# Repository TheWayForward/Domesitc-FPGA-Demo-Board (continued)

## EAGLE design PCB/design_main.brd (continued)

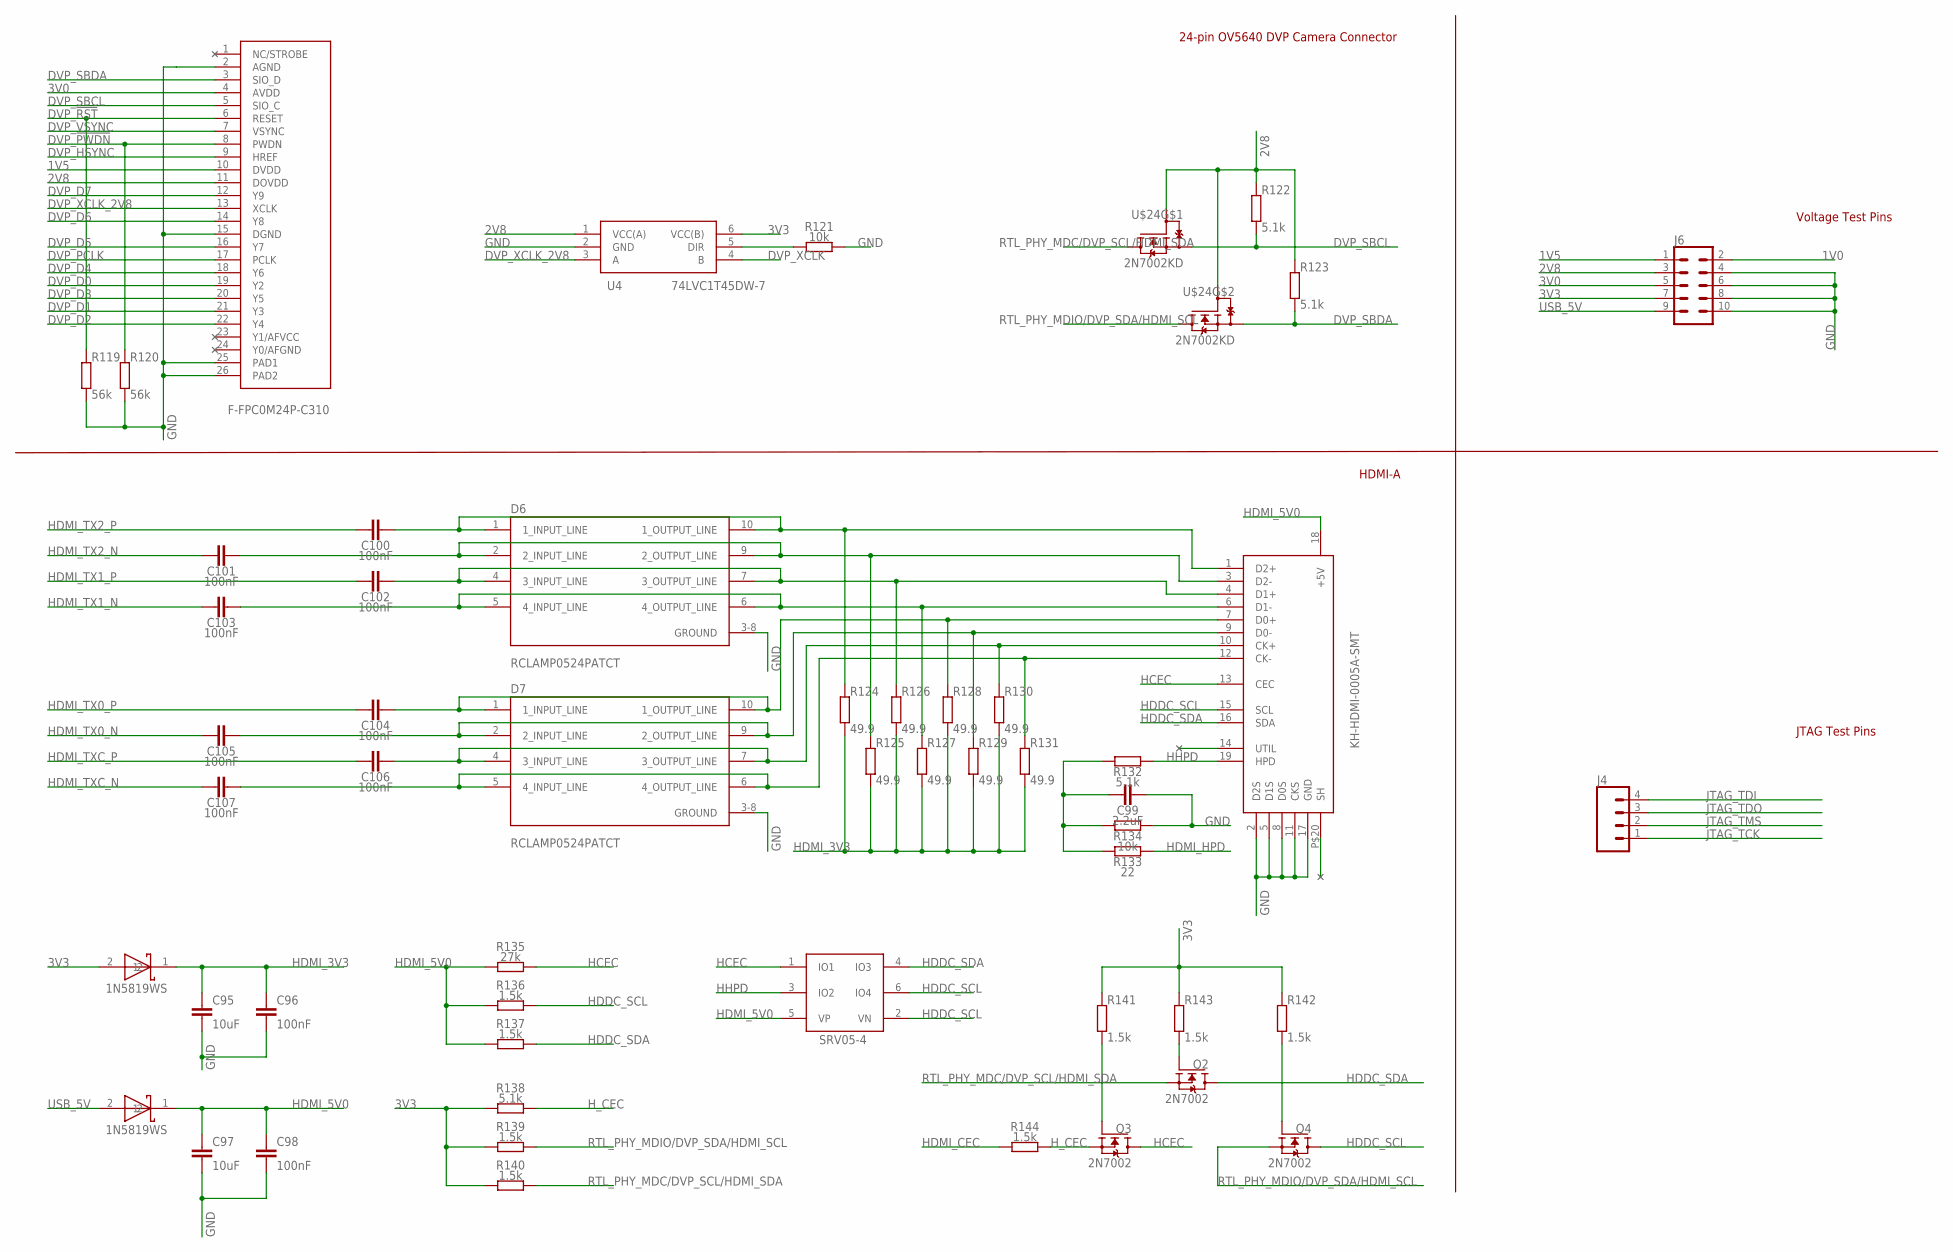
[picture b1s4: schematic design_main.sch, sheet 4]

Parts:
C95, C97: 10uF; C0805
C96, C98, C100, C101, C102, C103, C104, C105, C106, C107: 100nF; C0805
C99: 2.2uF; C0805
D6, D7: SEMTECH_RCLAMP0524PATCTSEMTECH_RCLAMP0524PATCT_0_0; SEMTECH_RCLAMP0524PATCT_0
J4: CONN_04PTH; 1X04
J6: CONN_05X2PTH; 2X5
Q2, Q3, Q4: 2N7002; SOT95P240X111-3N
R119, R120: 56k; R0805
R121, R134: 10k; R0805
R122, R123, R132, R138: 5.1k; R0805
R124, R125, R126, R127, R128, R129, R130, R131: 49.9; R0805
R133: 22; R0805
R135: 27k; R0805
R136, R137, R139, R140, R141, R142, R143, R144: 1.5k; R0805
U4: 74LVC1T45DW-7; SOT65P210X110-6N
U$23: F-FPC0M24P-C310
U$24: 2N7002KD
U$25, U$26: 1N5819WS
U$27: KH-HDMI-0005A-SMT
U$28: SRV05-4

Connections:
1V0: J6.2; also elsewhere on the board
1V5: J6.1, U$23.10 (DVDD); also elsewhere on the board
2V8: J6.3, R122.2, R123.2, U4.1 (VCC(A)), U$23.11 (DOVDD), U$24.P$2 (G1), U$24.P$5 (G2); also elsewhere on the board
3V0: J6.5, U$23.4 (AVDD); also elsewhere on the board
3V3: J6.7, R138.1, R139.1, R140.1, R141.1, R142.1, R143.1, U4.6 (VCC(B)), U$25.2; also elsewhere on the board
DVP_!PWDN!: R120.1, U$23.8 (PWDN); also elsewhere on the board
DVP_!RST!: R119.1, U$23.6 (RESET); also elsewhere on the board
DVP_D0: U$23.19 (Y2); also elsewhere on the board
DVP_D1: U$23.21 (Y3); also elsewhere on the board
DVP_D2: U$23.22 (Y4); also elsewhere on the board
DVP_D3: U$23.20 (Y5); also elsewhere on the board
DVP_D4: U$23.18 (Y6); also elsewhere on the board
DVP_D5: U$23.16 (Y7); also elsewhere on the board
DVP_D6: U$23.14 (Y8); also elsewhere on the board
DVP_D7: U$23.12 (Y9); also elsewhere on the board
DVP_HSYNC: U$23.9 (HREF); also elsewhere on the board
DVP_PCLK: U$23.17 (PCLK); also elsewhere on the board
DVP_SBCL: R122.1, U$23.5 (SIO_C), U$24.P$1 (S1)
DVP_SBDA: R123.1, U$23.3 (SIO_D), U$24.P$4 (S2)
DVP_VSYNC: U$23.7 (VSYNC); also elsewhere on the board
DVP_XCLK: U4.4 (B); also elsewhere on the board
DVP_XCLK_2V8: U4.3 (A), U$23.13 (XCLK)
GND: C95.1, C96.1, C97.1, C98.1, C99.1, D6.3-8 (GROUND), D7.3-8 (GROUND), J6.4, J6.6, J6.8, J6.10, R119.2, R120.2, R121.2, R134.2, U4.2 (GND), U$23.2 (AGND), U$23.15 (DGND), U$23.25 (PAD1), U$23.26 (PAD2), U$27.2 (D2S), U$27.5 (D1S), U$27.8 (D0S), U$27.11 (CKS), U$27.17 (GND); also elsewhere on the board
HCEC: Q3.3 (D), R135.2, U$27.13 (CEC), U$28.1 (IO1)
HDDC_SCL: Q4.3 (D), R136.2, U$27.15 (SCL), U$28.2 (VN), U$28.6 (IO4)
HDDC_SDA: Q2.3 (D), R137.2, U$27.16 (SDA), U$28.4 (IO3)
HDMI_3V3: C95.2, C96.2, R124.2, R125.2, R126.2, R127.2, R128.2, R129.2, R130.2, R131.2, U$25.1
HDMI_5V0: C97.2, C98.2, R135.1, R136.1, R137.1, U$26.1, U$27.18 (+5V), U$28.5 (VP)
HDMI_CEC: R144.1; also elsewhere on the board
HDMI_HPD: R133.2; also elsewhere on the board
HDMI_TX0_N: C105.2; also elsewhere on the board
HDMI_TX0_P: C104.2; also elsewhere on the board
HDMI_TX1_N: C103.2; also elsewhere on the board
HDMI_TX1_P: C102.2; also elsewhere on the board
HDMI_TX2_N: C101.2; also elsewhere on the board
HDMI_TX2_P: C100.2; also elsewhere on the board
HDMI_TXC_N: C107.2; also elsewhere on the board
HDMI_TXC_P: C106.2; also elsewhere on the board
HHPD: R132.2, U$27.19 (HPD), U$28.3 (IO2)
H_CEC: Q3.2 (S), R138.2, R144.2
JTAG_TCK: J4.1; also elsewhere on the board
JTAG_TDI: J4.4; also elsewhere on the board
JTAG_TDO: J4.3; also elsewhere on the board
JTAG_TMS: J4.2; also elsewhere on the board
unnamed: R121.1, U4.5 (DIR)
unnamed: C100.1, D6.1 (1_INPUT_LINE), D6.10 (1_OUTPUT_LINE), R124.1, U$27.1 (D2+)
unnamed: C101.1, D6.2 (2_INPUT_LINE), D6.9 (2_OUTPUT_LINE), R125.1, U$27.3 (D2-)
unnamed: C102.1, D6.4 (3_INPUT_LINE), D6.7 (3_OUTPUT_LINE), R126.1, U$27.4 (D1+)
unnamed: C103.1, D6.5 (4_INPUT_LINE), D6.6 (4_OUTPUT_LINE), R127.1, U$27.6 (D1-)
unnamed: C104.1, D7.1 (1_INPUT_LINE), D7.10 (1_OUTPUT_LINE), R128.1, U$27.7 (D0+)
unnamed: C105.1, D7.2 (2_INPUT_LINE), D7.9 (2_OUTPUT_LINE), R129.1, U$27.9 (D0-)
unnamed: C106.1, D7.4 (3_INPUT_LINE), D7.7 (3_OUTPUT_LINE), R130.1, U$27.10 (CK+)
unnamed: C107.1, D7.5 (4_INPUT_LINE), D7.6 (4_OUTPUT_LINE), R131.1, U$27.12 (CK-)
unnamed: C99.2, R132.1, R133.1, R134.1
unnamed: Q2.1 (G), R143.2
unnamed: Q3.1 (G), R141.2
unnamed: Q4.1 (G), R142.2
RTL_PHY_MDC/DVP_SCL/HDMI_SDA: Q2.2 (S), R140.2, U$24.P$6 (D1); also elsewhere on the board
RTL_PHY_MDIO/DVP_SDA/HDMI_SCL: Q4.2 (S), R139.2, U$24.P$3 (D2); also elsewhere on the board
USB_5V: J6.9, U$26.2; also elsewhere on the board

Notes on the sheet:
24-pin OV5640 DVP Camera Connector
HDMI-A
Voltage Test Pins
JTAG Test Pins

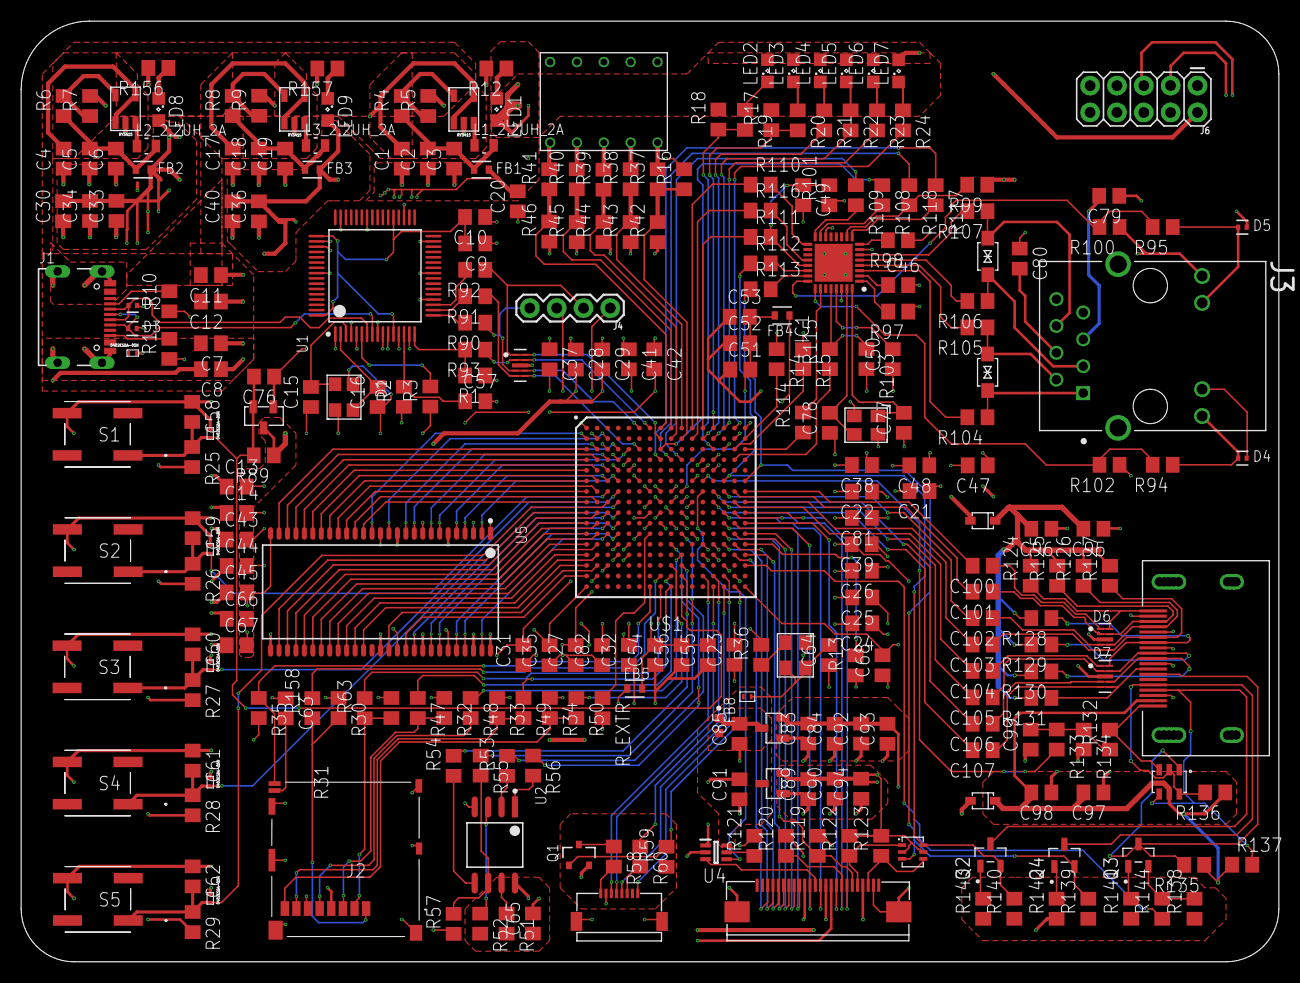
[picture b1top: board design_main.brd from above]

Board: 4 copper layers, 119.0 x 89.0 mm, 288 parts (0 on the bottom side), 235 nets.

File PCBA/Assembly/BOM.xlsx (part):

Description | Comment | Designator | Footprint | 编号
贴片电阻 | 1kΩ | R1 | R0805 | C17513
贴片电阻 | 10kΩ | R2 | R0805 | C844893
贴片电阻 | 12kΩ | R3 | R0805 | C706254
贴片电阻 | 680kΩ | R4 | R0805 | C445667
贴片电阻 | 150kΩ | R5 | R0805 | C17470
贴片电阻 | 150kΩ | R6 | R0805 | C17470
贴片电阻 | 100kΩ | R7 | R0805 | C161786
贴片电阻 | 100kΩ | R8 | R0805 | C161786
贴片电阻 | 150kΩ | R9 | R0805 | C17470
贴片电阻 | 5.1kΩ | R10 | R0805 | C2094165
贴片电阻 | 5.1kΩ | R11 | R0805 | C2094165
贴片电阻 | 220Ω | R12 | R0805 | C445664
贴片电阻 | 4.7kΩ | R13 | R0805 | C17673
贴片电阻 | 4.7kΩ | R14 | R0805 | C17673
贴片电阻 | 4.7kΩ | R15 | R0805 | C17673
贴片电阻 | 4.7kΩ | R16 | R0805 | C17673
贴片电阻 | 4.7kΩ | R17 | R0805 | C17673
贴片电阻 | 4.7kΩ | R18 | R0805 | C17673
贴片电阻 | 510Ω | R19 | R0805 | C17734
贴片电阻 | 510Ω | R20 | R0805 | C17734
贴片电阻 | 510Ω | R21 | R0805 | C17734
贴片电阻 | 510Ω | R22 | R0805 | C17734
贴片电阻 | 510Ω | R23 | R0805 | C17734
贴片电阻 | 510Ω | R24 | R0805 | C17734
贴片电阻 | 10kΩ | R25 | R0805 | C17414
贴片电阻 | 10kΩ | R26 | R0805 | C17414
贴片电阻 | 10kΩ | R27 | R0805 | C17414
贴片电阻 | 10kΩ | R28 | R0805 | C17414
贴片电阻 | 10kΩ | R29 | R0805 | C17414
贴片电阻 | 10kΩ | R30 | R0805 | C17414
贴片电阻 | 10kΩ | R31 | R0805 | C17414
贴片电阻 | 10kΩ | R32 | R0805 | C17414
贴片电阻 | 10kΩ | R33 | R0805 | C17414
贴片电阻 | 10kΩ | R34 | R0805 | C17414
贴片电阻 | 4.7kΩ | R35 | R0805 | C17673
贴片电阻 | 22Ω | R36 | R0805 | C445659
贴片电阻 | 165Ω | R37 | R0805 | C409974
贴片电阻 | 1.5kΩ | R38 | R0805 | C4310
贴片电阻 | 1.5kΩ | R39 | R0805 | C4310
贴片电阻 | 1.5kΩ | R40 | R0805 | C4310
贴片电阻 | 1.5kΩ | R41 | R0805 | C4310
贴片电阻 | 510Ω | R42 | R0805 | C17734
贴片电阻 | 13kΩ | R43 | R0805 | C17455
贴片电阻 | 13kΩ | R44 | R0805 | C17455
贴片电阻 | 13kΩ | R45 | R0805 | C17455
贴片电阻 | 13kΩ | R46 | R0805 | C17455
贴片电阻 | 33Ω | R47 | R0805 | C706236
贴片电阻 | 33Ω | R48 | R0805 | C706236
贴片电阻 | 33Ω | R49 | R0805 | C706236
贴片电阻 | 33Ω | R50 | R0805 | C706236
贴片电阻 | 4.7kΩ | R51 | R0805 | C17673
贴片电阻 | 4.7kΩ | R52 | R0805 | C17673
贴片电阻 | 33Ω | R53 | R0805 | C706236
贴片电阻 | 33Ω | R54 | R0805 | C706236
贴片电阻 | 33Ω | R55 | R0805 | C706236
贴片电阻 | 33Ω | R56 | R0805 | C706236
贴片电阻 | 1kΩ | R57 | R0805 | C17513
贴片电阻 | 10Ω | R58 | R0805 | C17470
贴片电阻 | 4.7kΩ | R59 | R0805 | C17673
贴片电阻 | 22Ω | R60 | R0805 | C445659
贴片电阻 | 33Ω | R63 | R0805 | C706236
贴片电阻 | 150kΩ | R89 | R0805 | C17470
贴片电阻 | 33Ω | R90 | R0805 | C706236
贴片电阻 | 33Ω | R91 | R0805 | C706236
贴片电阻 | 33Ω | R92 | R0805 | C706236
贴片电阻 | 33Ω | R93 | R0805 | C706236
贴片电阻 | 510Ω | R94 | R0805 | C17734
贴片电阻 | 510Ω | R95 | R0805 | C17734
贴片电阻 | 2.49kΩ | R97 | R0805 | C17470
贴片电阻 | 5.1kΩ | R98 | R0805 | C2094165
贴片电阻 | 5.1kΩ | R99 | R0805 | C2094165
贴片电阻 | 5.1kΩ | R100 | R0805 | C2094165
贴片电阻 | 5.1kΩ | R101 | R0805 | C2094165
贴片电阻 | 5.1kΩ | R102 | R0805 | C2094165
贴片电阻 | 5.1kΩ | R103 | R0805 | C2094165
贴片电阻 | 22Ω | R104 | R0805 | C445659
贴片电阻 | 22Ω | R105 | R0805 | C445659
贴片电阻 | 22Ω | R106 | R0805 | C445659
贴片电阻 | 22Ω | R107 | R0805 | C445659
贴片电阻 | 22Ω | R108 | R0805 | C445659
贴片电阻 | 22Ω | R109 | R0805 | C445659
贴片电阻 | 22Ω | R110 | R0805 | C445659
贴片电阻 | 22Ω | R111 | R0805 | C445659
贴片电阻 | 22Ω | R112 | R0805 | C445659
贴片电阻 | 22Ω | R113 | R0805 | C445659
贴片电阻 | 22Ω | R114 | R0805 | C445659
贴片电阻 | 22Ω | R115 | R0805 | C445659
贴片电阻 | 22Ω | R116 | R0805 | C445659
贴片电阻 | 22Ω | R117 | R0805 | C445659
贴片电阻 | 22Ω | R118 | R0805 | C445659
贴片电阻 | 56kΩ | R119 | R0805 | C17470
贴片电阻 | 56kΩ | R120 | R0805 | C17470
贴片电阻 | 10kΩ | R121 | R0805 | C17414
贴片电阻 | 5.1kΩ | R122 | R0805 | C2094165
贴片电阻 | 5.1kΩ | R123 | R0805 | C2094165
贴片电阻 | 49.9Ω | R124 | R0805 | C17414
贴片电阻 | 49.9Ω | R125 | R0805 | C17414
贴片电阻 | 49.9Ω | R126 | R0805 | C17414
贴片电阻 | 49.9Ω | R127 | R0805 | C17414
贴片电阻 | 49.9Ω | R128 | R0805 | C17414
贴片电阻 | 49.9Ω | R129 | R0805 | C17414
贴片电阻 | 49.9Ω | R130 | R0805 | C17414
贴片电阻 | 49.9Ω | R131 | R0805 | C17414
贴片电阻 | 5.1kΩ | R132 | R0805 | C2094165
贴片电阻 | 22Ω | R133 | R0805 | C445659
贴片电阻 | 10kΩ | R134 | R0805 | C17414
贴片电阻 | 27kΩ | R135 | R0805 | C17593
贴片电阻 | 1.5kΩ | R136 | R0805 | C4310
贴片电阻 | 1.5kΩ | R137 | R0805 | C4310
贴片电阻 | 5.1kΩ | R138 | R0805 | C2094165
贴片电阻 | 1.5kΩ | R139 | R0805 | C4310
贴片电阻 | 1.5kΩ | R140 | R0805 | C4310
贴片电阻 | 1.5kΩ | R141 | R0805 | C4310
贴片电阻 | 1.5kΩ | R142 | R0805 | C4310
贴片电阻 | 1.5kΩ | R143 | R0805 | C4310
贴片电阻 | 1.5kΩ | R144 | R0805 | C4310
贴片电阻 | 220Ω | R156 | R0805 | C445664
贴片电阻 | 220Ω | R157 | R0805 | C445664
贴片电阻 | 33Ω | R158 | R0805 | C706236
贴片电容 | 10uF | C1 | C0805 | C2932476
贴片电容 | 100nF | C2 | C0805 | C1711
贴片电容 | 10uF | C3 | C0805 | C2932476
贴片电容 | 10uF | C4 | C0805 | C2932476
贴片电容 | 100nF | C5 | C0805 | C1711
贴片电容 | 10uF | C6 | C0805 | C2932476
贴片电容 | 22uF | C7 | C0805 | C338080
贴片电容 | 22uF | C8 | C0805 | C338080
贴片电容 | 1uF | C9 | C0805 | C28323
贴片电容 | 1uF | C10 | C0805 | C28323
贴片电容 | 22uF | C11 | C0805 | C338080
贴片电容 | 22uF | C12 | C0805 | C338080
贴片电容 | 100nF | C13 | C0805 | C1711
贴片电容 | 100nF | C14 | C0805 | C1711
贴片电容 | 22pF | C15 | C0805 | C1804
贴片电容 | 22pF | C16 | C0805 | C1804
贴片电容 | 10uF | C17 | C0805 | C2932476
贴片电容 | 100nF | C18 | C0805 | C1711
贴片电容 | 10uF | C19 | C0805 | C2932476
贴片电容 | 100nF | C20 | C0805 | C1711
贴片电容 | 100nF | C21 | C0805 | C1711
贴片电容 | 100nF | C22 | C0805 | C1711
贴片电容 | 100nF | C23 | C0805 | C1711
贴片电容 | 100nF | C24 | C0805 | C1711
贴片电容 | 100nF | C25 | C0805 | C1711
贴片电容 | 100nF | C26 | C0805 | C1711
贴片电容 | 100nF | C27 | C0805 | C1711
贴片电容 | 100nF | C28 | C0805 | C1711
贴片电容 | 100nF | C29 | C0805 | C1711
贴片电容 | 100nF | C30 | C0805 | C1711
贴片电容 | 100nF | C31 | C0805 | C1711
贴片电容 | 100nF | C32 | C0805 | C1711
贴片电容 | 10uF | C33 | C0805 | C2932476
贴片电容 | 10uF | C34 | C0805 | C2932476
贴片电容 | 100nF | C35 | C0805 | C1711
贴片电容 | 100nF | C36 | C0805 | C1711
贴片电容 | 100nF | C37 | C0805 | C1711
贴片电容 | 100nF | C38 | C0805 | C1711
贴片电容 | 100nF | C39 | C0805 | C1711
贴片电容 | 100nF | C40 | C0805 | C1711
贴片电容 | 4.7uF | C41 | C0805 | C1779
贴片电容 | 100nF | C42 | C0805 | C1711
贴片电容 | 100nF | C43 | C0805 | C1711
贴片电容 | 100nF | C44 | C0805 | C1711
贴片电容 | 100nF | C45 | C0805 | C1711
贴片电容 | 100nF | C46 | C0805 | C1711
贴片电容 | 10uF | C47 | C0805 | C2932476
贴片电容 | 100nF | C48 | C0805 | C1711
贴片电容 | 1nF | C49 | C0805 | C46653
贴片电容 | 100nF | C50 | C0805 | C1711
贴片电容 | 10uF | C51 | C0805 | C2932476
贴片电容 | 100nF | C52 | C0805 | C1711
贴片电容 | 10nF | C53 | C0805 | C441760
贴片电容 | 10uF | C54 | C0805 | C2932476
贴片电容 | 100nF | C55 | C0805 | C1711
贴片电容 | 10nF | C56 | C0805 | C441760
贴片电容 | 100nF | C57 | C0805 | C1711
贴片电容 | 100nF | C58 | C0805 | C1711
贴片电容 | 100nF | C59 | C0805 | C1711
贴片电容 | 100nF | C60 | C0805 | C1711
贴片电容 | 100nF | C61 | C0805 | C1711
贴片电容 | 100nF | C62 | C0805 | C1711
贴片电容 | 2.2uF | C63 | C0805 | C19110
贴片电容 | 100nF | C64 | C0805 | C1711
贴片电容 | 100nF | C65 | C0805 | C1711
贴片电容 | 100nF | C66 | C0805 | C1711
贴片电容 | 100nF | C67 | C0805 | C1711
贴片电容 | 100nF | C68 | C0805 | C1711
贴片电容 | 100nF | C76 | C0805 | C1711
贴片电容 | 18pF | C77 | C0805 | C527079
贴片电容 | 18pF | C78 | C0805 | C527079
贴片电容 | 1nF | C79 | C0805 | C909887
贴片电容 | 1nF | C80 | C0805 | C909887
贴片电容 | 100nF | C81 | C0805 | C1711
贴片电容 | 100nF | C82 | C0805 | C1711
贴片电容 | 22uF | C83 | C0805 | C338080
贴片电容 | 100nF | C84 | C0805 | C1711
贴片电容 | 100nF | C85 | C0805 | C1711
贴片电容 | 10uF | C89 | C0805 | C2932476
贴片电容 | 100nF | C90 | C0805 | C1711
贴片电容 | 100nF | C91 | C0805 | C1711
贴片电容 | 22uF | C92 | C0805 | C338080
贴片电容 | 100nF | C93 | C0805 | C1711
贴片电容 | 100nF | C94 | C0805 | C1711
贴片电容 | 10uF | C95 | C0805 | C2932476
贴片电容 | 100nF | C96 | C0805 | C1711
贴片电容 | 10uF | C97 | C0805 | C2932476
贴片电容 | 100nF | C98 | C0805 | C1711
贴片电容 | 2.2uF | C99 | C0805 | C19110
贴片电容 | 100nF | C100 | C0805 | C1711
贴片电容 | 100nF | C101 | C0805 | C1711
贴片电容 | 100nF | C102 | C0805 | C1711
贴片电容 | 100nF | C103 | C0805 | C1711
贴片电容 | 100nF | C104 | C0805 | C1711
贴片电容 | 100nF | C105 | C0805 | C1711
贴片电容 | 100nF | C106 | C0805 | C1711
贴片电容 | 100nF | C107 | C0805 | C1711
ESD保护 | SEMTECH_RCLAMP0524PATCT | D1 | SLP2510-8 | C40960
瞬态抑制二极管 | MURATA_LXES15AAA1-153 | D2 | 0402 | C86141
瞬态抑制二极管 | MURATA_LXES15AAA1-153 | D3 | 0402 | C86141
瞬态抑制二极管 | MURATA_LXES15AAA1-153 | D4 | 0402 | C86141
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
